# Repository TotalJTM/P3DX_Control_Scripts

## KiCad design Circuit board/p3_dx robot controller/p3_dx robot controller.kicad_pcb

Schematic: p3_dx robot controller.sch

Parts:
A1: Arduino_UNO_R3
C1: 10uF; C_1206_3216Metric_Pad1.33x1.80mm_HandSolder
P1: PowerPlug; Molex_Micro-Fit_3.0_43650-0415_1x04_P3.00mm_Vertical
P2: PowerBoard; PinHeader_2x13_P2.54mm_Vertical
P3: SonarBoard; PinHeader_2x05_P2.54mm_Vertical
P4: InterfaceBoard; PinHeader_2x08_P2.54mm_Vertical
U1: ATtiny84-20PU; DIP-14_W7.62mm

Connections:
AUX_SWITCH: A1.27 (D12), P4.6
BUZZER: A1.24 (D9), P4.8
E-STOP: P2.7
GND: A1.6 (GND), A1.7 (GND), A1.29 (GND), C1.1, P1.2, P2.23, P2.25, P3.8, P3.9, P4.12, P4.13, U1.2 (XTAL1/PB0), U1.3 (XTAL2/PB1), U1.6 (PA7), U1.14 (GND)
LEFT_ENCODER_A: A1.9 (A0), P2.6
LEFT_ENCODER_B: A1.12 (A3), P2.12
LEFT_MOTOR_DIR: A1.23 (D8), P2.2
LEFT_MOTOR_PWM: A1.21 (D6), P2.1
MOTORS_ENABLED: A1.19 (D4), P2.5
MOTOR_SWITCH: A1.17 (D2), P4.4
POWER_LED: A1.25 (D10), P4.9
RADIO_SWITCH: A1.28 (D13), P4.5
RESET: A1.3 (~RESET), U1.4 (~RESET~/PB3)
RESET_SWITCH: A1.18 (D3), P4.3
RIGHT_ENCODER_A: A1.10 (A1), P2.8
RIGHT_ENCODER_B: A1.11 (A2), P2.10
RIGHT_MOTOR_DIR: A1.22 (D7), P2.4
RIGHT_MOTOR_PWM: A1.20 (D5), P2.3
SCL: A1.14 (SCL/A5), U1.5 (PB2)
SDA: A1.13 (SDA/A4), U1.7 (PA6)
SERIAL_IN: A1.15 (D0/RX)
SERIAL_OUT: A1.16 (D1/TX)
STATUS_LED: A1.26 (D11), P4.10
S_ECHO: P3.10, U1.9 (PA4)
S_INHIB: P3.4, U1.10 (PA3)
S_SEL1: P3.1, U1.13 (AREF/PA0)
S_SEL2: P3.2, U1.12 (PA1)
S_SEL3: P3.3, U1.11 (PA2)
S_TRIG: P3.5, U1.8 (PA5)
VCC: A1.8 (VIN), C1.2, P1.3, P3.6, P3.7, P4.1, P4.2, U1.1 (VCC)
VPP: P1.1, P2.22, P4.11

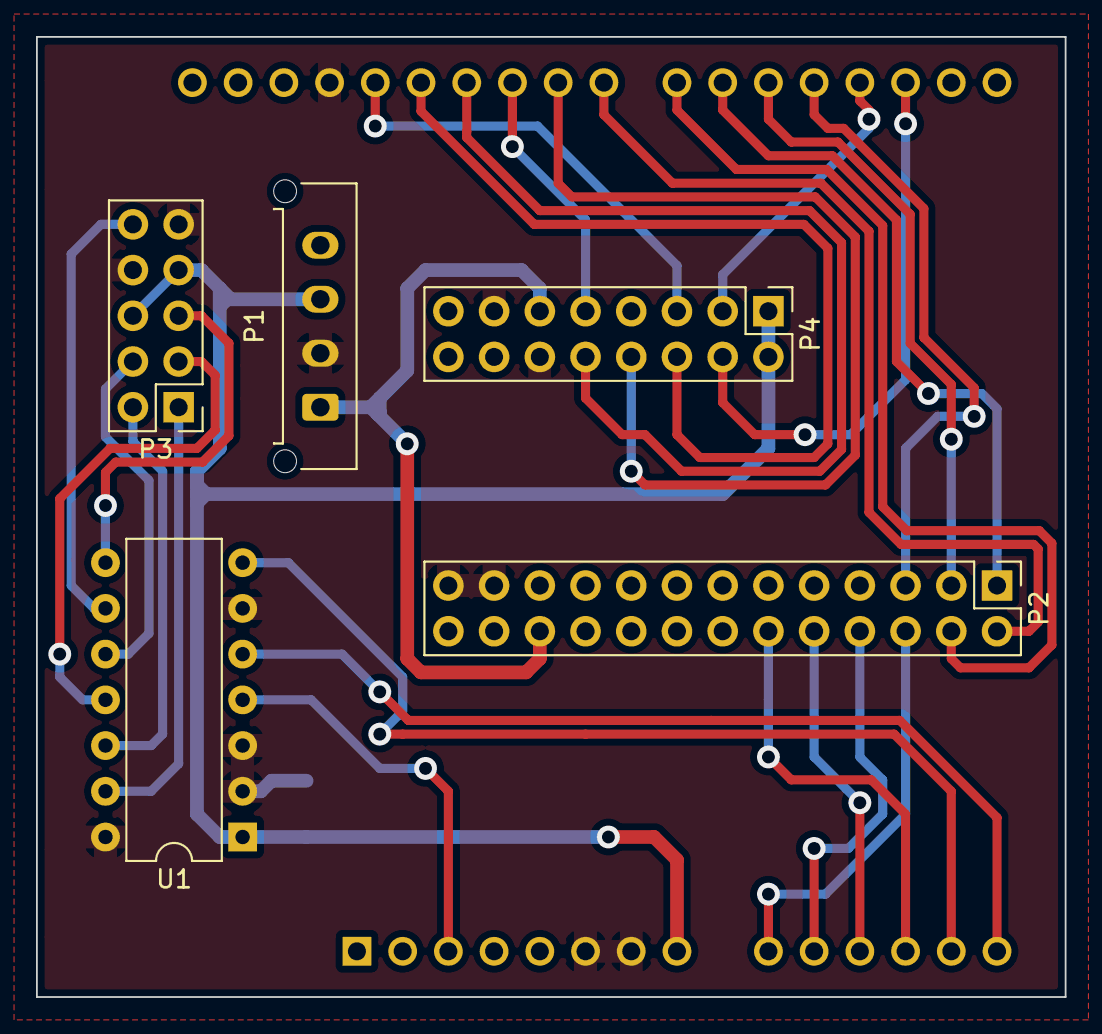
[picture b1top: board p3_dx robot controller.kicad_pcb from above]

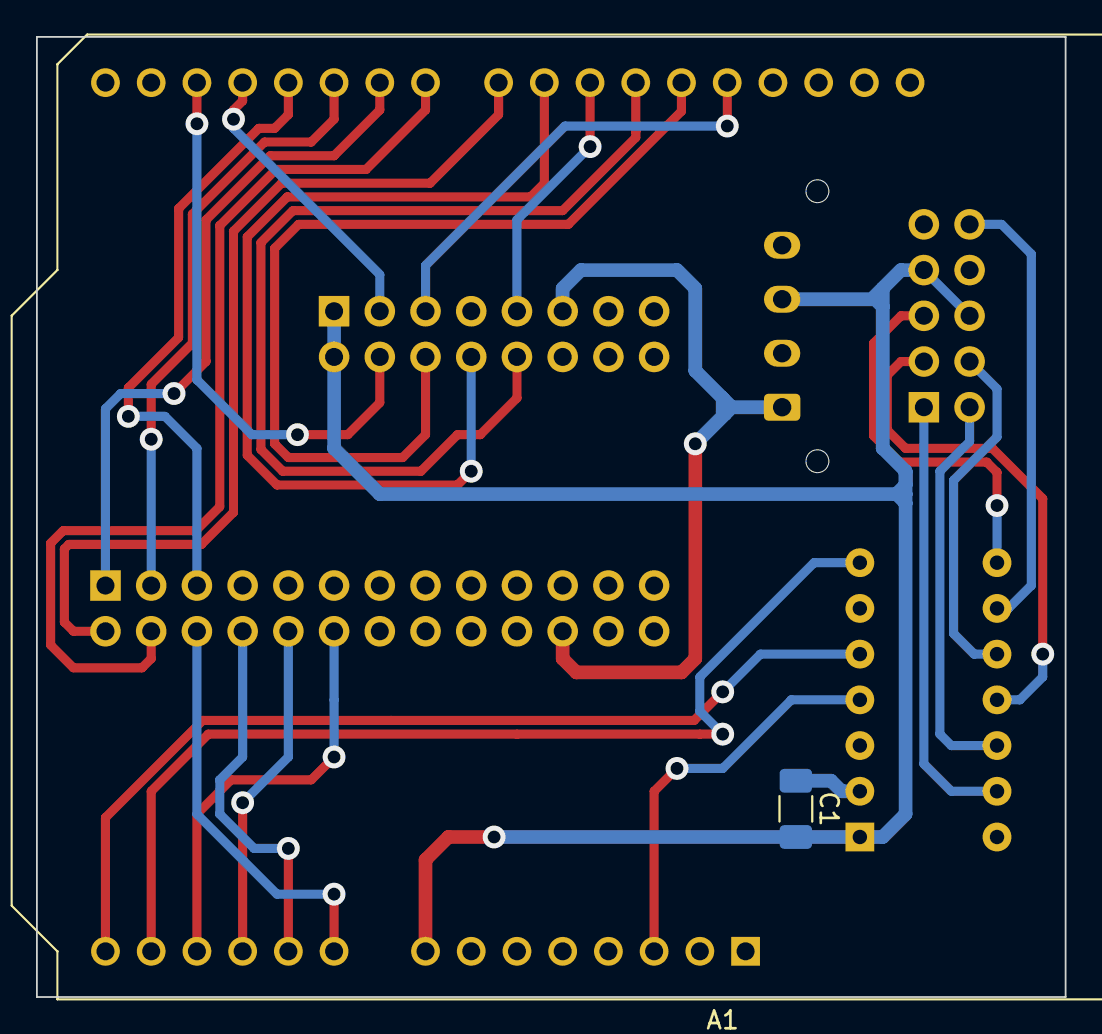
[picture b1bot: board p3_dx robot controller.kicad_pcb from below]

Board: 2 copper layers, 57.1 x 53.3 mm, 7 parts (2 on the bottom side), 28 nets.

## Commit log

2021-08-07 added other main files
2021-08-08 network.py testing
2021-08-08 more network.py testing
2021-08-08 even more network.py testing
2021-08-08 added comms functionality with network.py and robot_communications.py
2021-08-08 even more network.py testing 2
2021-08-13 moved from command based messages top json keys/vals
2021-08-14 added serial comms functionality
2021-08-14 minor changes to serial comms and main, working on RPI
2021-08-15 changed how messages are sent, now uses timers to make communication more consistent
2021-08-16 base station now has tank and single joystick driving modes, added rest of robot code (controller, base station files)
2021-08-19 fixed issues from last commit and added method of getting encoder values from arduino
2021-08-19 updates to base_network, rpi scripts and arduino script
2021-08-21 added PID to arduino with command to overwrite PID vars
2021-08-21 added threading for socket and a parameter to allow direct drive without using the PID controller
2021-08-22 added button functionality and code is set for robot usage
2021-08-22 added a music box for the buzzer (just for fun), can now play keyboard cat,mii channel them and tetris (will program better ones later, these will do for testing)
2021-08-22 added comments to all the rpi files, seperated controller items from base_network and started a main file
2021-08-23 code is working properly, controller threading is working reliably and the socket duplicate issue has been fixed
2021-08-23 last push had some errors, they are now fixed and the code runs on the RPI
